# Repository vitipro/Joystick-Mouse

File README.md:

# Joystick-Mouse
Proyecto de creación de un Mouse tipo Joystick desde 0. Incluído el diseño de la PCB + casing.

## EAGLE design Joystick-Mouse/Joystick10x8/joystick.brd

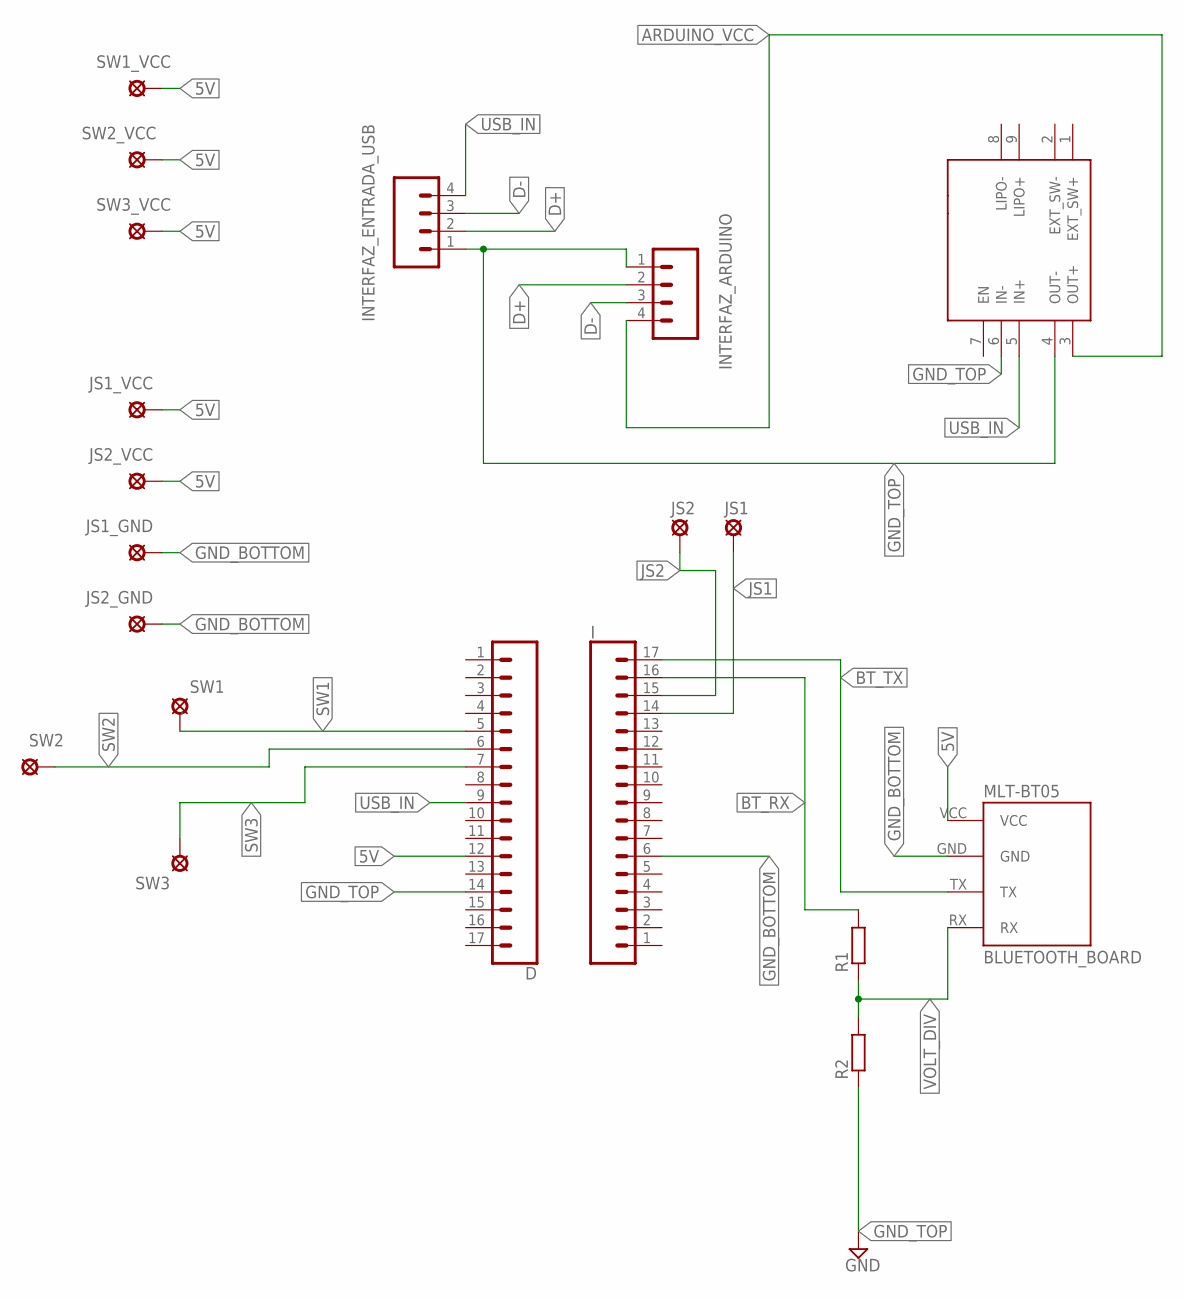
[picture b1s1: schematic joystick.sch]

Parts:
D: CONN_17; 1X17
I: CONN_17; 1X17
INTERFAZ_ARDUINO: CONN_04; 1X04
INTERFAZ_ENTRADA_USB: CONN_04; 1X04
JS1, JS1_GND, JS1_VCC, JS2, JS2_GND, JS2_VCC: MCS08
LIPO_BOOSTER: LIP_CHARGER_LAYOUT; LIP_CHARGER_FOOTPRINT
MLT-BT05: BLUETOOTH_BOARD; BT_BOARD_FOOTPRINT
R1, R2: R-EU_R0805; R0805
SW1, SW1_VCC, SW2, SW2_VCC, SW3, SW3_VCC: MCS08

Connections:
5V: D.12, JS1_VCC.MP, JS2_VCC.MP, MLT-BT05.VCC, SW1_VCC.MP, SW2_VCC.MP, SW3_VCC.MP
ARDUINO_VCC: INTERFAZ_ARDUINO.4, LIPO_BOOSTER.3 (OUT+)
BT_RX: I.16, R1.2
BT_TX: I.17, MLT-BT05.TX
D+: INTERFAZ_ARDUINO.2, INTERFAZ_ENTRADA_USB.2
D-: INTERFAZ_ARDUINO.3, INTERFAZ_ENTRADA_USB.3
GND_BOTTOM: I.6, JS1_GND.MP, JS2_GND.MP, MLT-BT05.GND
GND_TOP: D.14, INTERFAZ_ARDUINO.1, INTERFAZ_ENTRADA_USB.1, LIPO_BOOSTER.4 (OUT-), LIPO_BOOSTER.6 (IN-), R2.1
JS1: I.14, JS1.MP
JS2: I.15, JS2.MP
SW1: D.5, SW1.MP
SW2: D.6, SW2.MP
SW3: D.7, SW3.MP
USB_IN: D.9, INTERFAZ_ENTRADA_USB.4, LIPO_BOOSTER.5 (IN+)
VOLT_DIV: MLT-BT05.RX, R1.1, R2.2

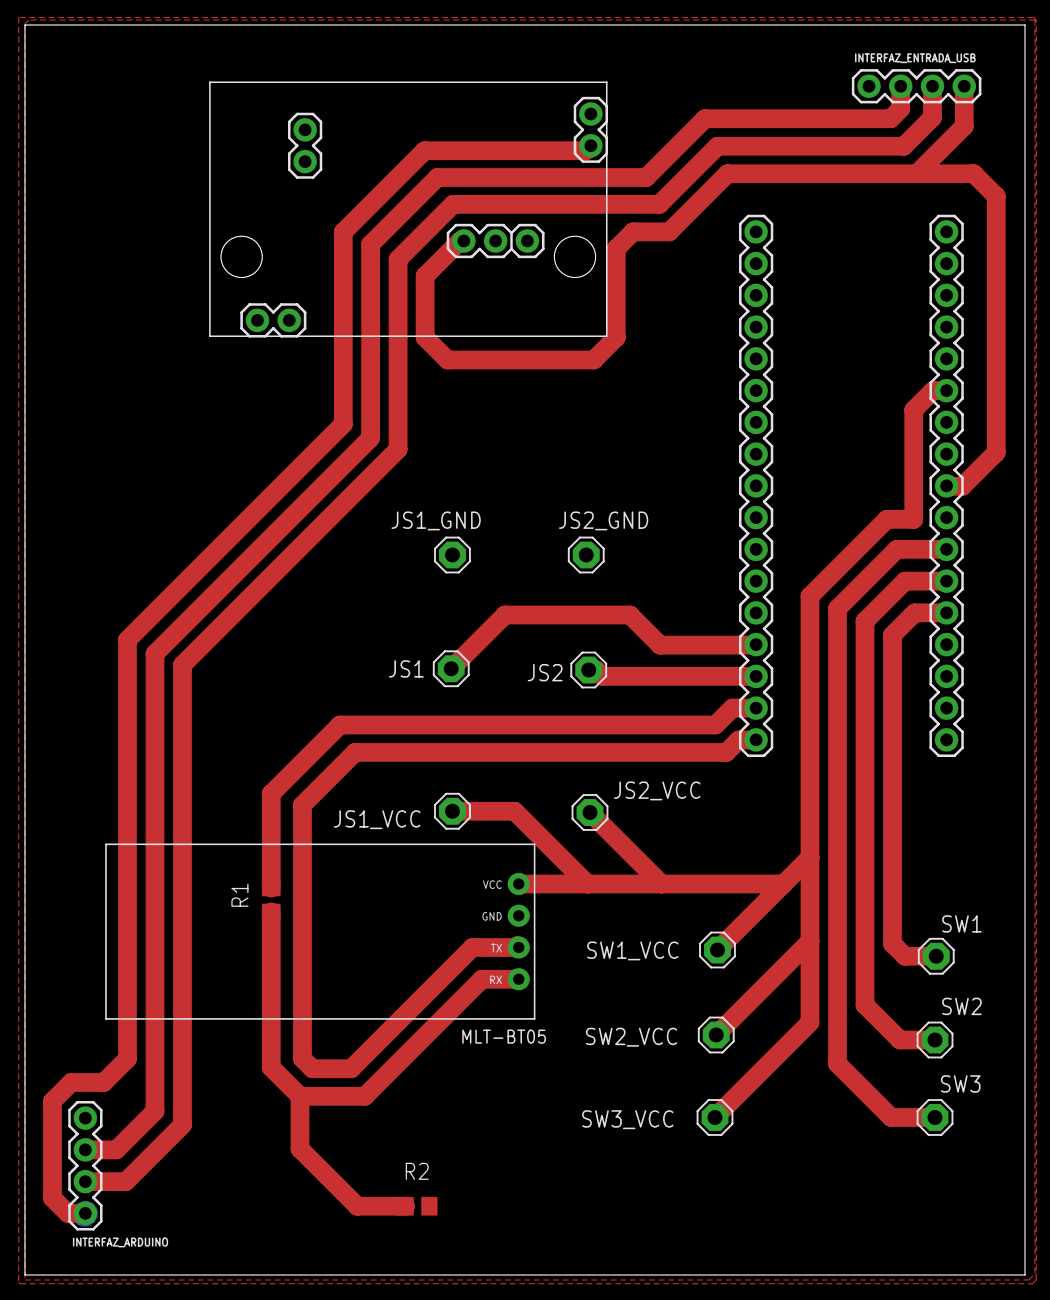
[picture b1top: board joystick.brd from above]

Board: 2 copper layers, 80.0 x 100.0 mm, 20 parts (0 on the bottom side), 15 nets.

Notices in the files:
parts and their libraries:
SparkFun-Connectors: Licensing: Creative Commons ShareAlike 4.0 International - https://creativecommons.org/licenses/by-sa/4.0
